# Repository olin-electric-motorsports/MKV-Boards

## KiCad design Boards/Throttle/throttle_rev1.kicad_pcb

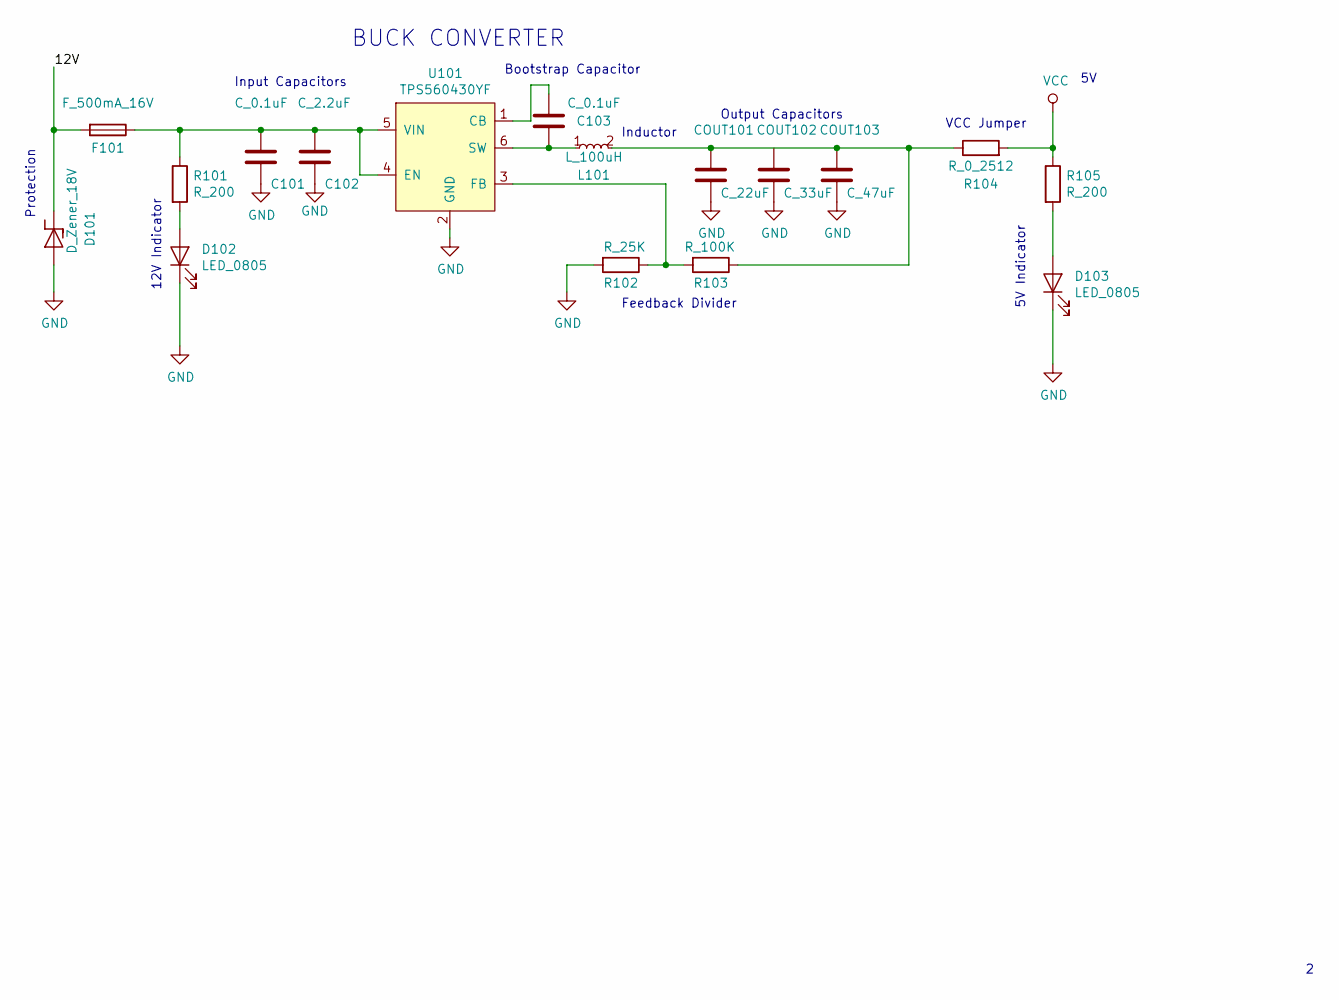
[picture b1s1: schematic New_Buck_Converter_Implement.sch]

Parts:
C101, C103: C_0.1uF; C_0805_OEM; MPN 478-3352-1-ND
C102: C_2.2uF; C_0603_1608Metric; MPN 311-1451-1-ND
COUT101: C_22uF; C_1206_OEM; MPN 445-11693-1-ND
COUT102: C_33uF; Fuse_1812; MPN 445-3924-1-ND
COUT103: C_47uF; C_0805_OEM; MPN 1276-6467-1-ND
D101: D_Zener_18V; DO-214AA; MPN SMBJ5355B-TPMSCT-ND
D102, D103: LED_0805; LED_0805_OEM; MPN 475-1410-1-ND
F101: F_500mA_16V; Fuse_1210; MPN 507-1786-1-ND
L101: L_100uH; MPN 445-15759-1-ND
R101, R105: R_200; R_0805_OEM; MPN RMCF0805JT200RCT-ND
R102: R_25K; R_0805_OEM; Digi-key Part Number CPF-A-0805B25KE
R103: R_100K; R_0805_OEM; MPN P100KCCT-ND
R104: R_0_2512; R_2512_OEM; MPN A121322CT-ND
U101: TPS560430YF; SOT-23-6_Handsoldering; MPN TPS560430YFDBVR

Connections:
+12V: D101.1 (K), F101.2; also elsewhere on the board
GND: C101.2, C102.2, COUT101.2, COUT102.2, COUT103.2, D101.2 (A), D102.1 (K), D103.1 (K), R102.2, U101.2 (GND); also elsewhere on the board
unnamed: C101.1, C102.1, F101.1, R101.1, U101.4 (EN), U101.5 (VIN)
unnamed: C103.1, L101.1, U101.6 (SW)
unnamed: C103.2, U101.1 (CB)
unnamed: D102.2 (A), R101.2
unnamed: D103.2 (A), R105.2
unnamed: R102.1, R103.2, U101.3 (FB)
VCC: R104.2, R105.1; also elsewhere on the board

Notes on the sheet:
Input Capacitors
12V Indicator
Protection
BUCK CONVERTER
Feedback Divider
Inductor
Bootstrap Capacitor
Output Capacitors
VCC Jumper
5V Indicator

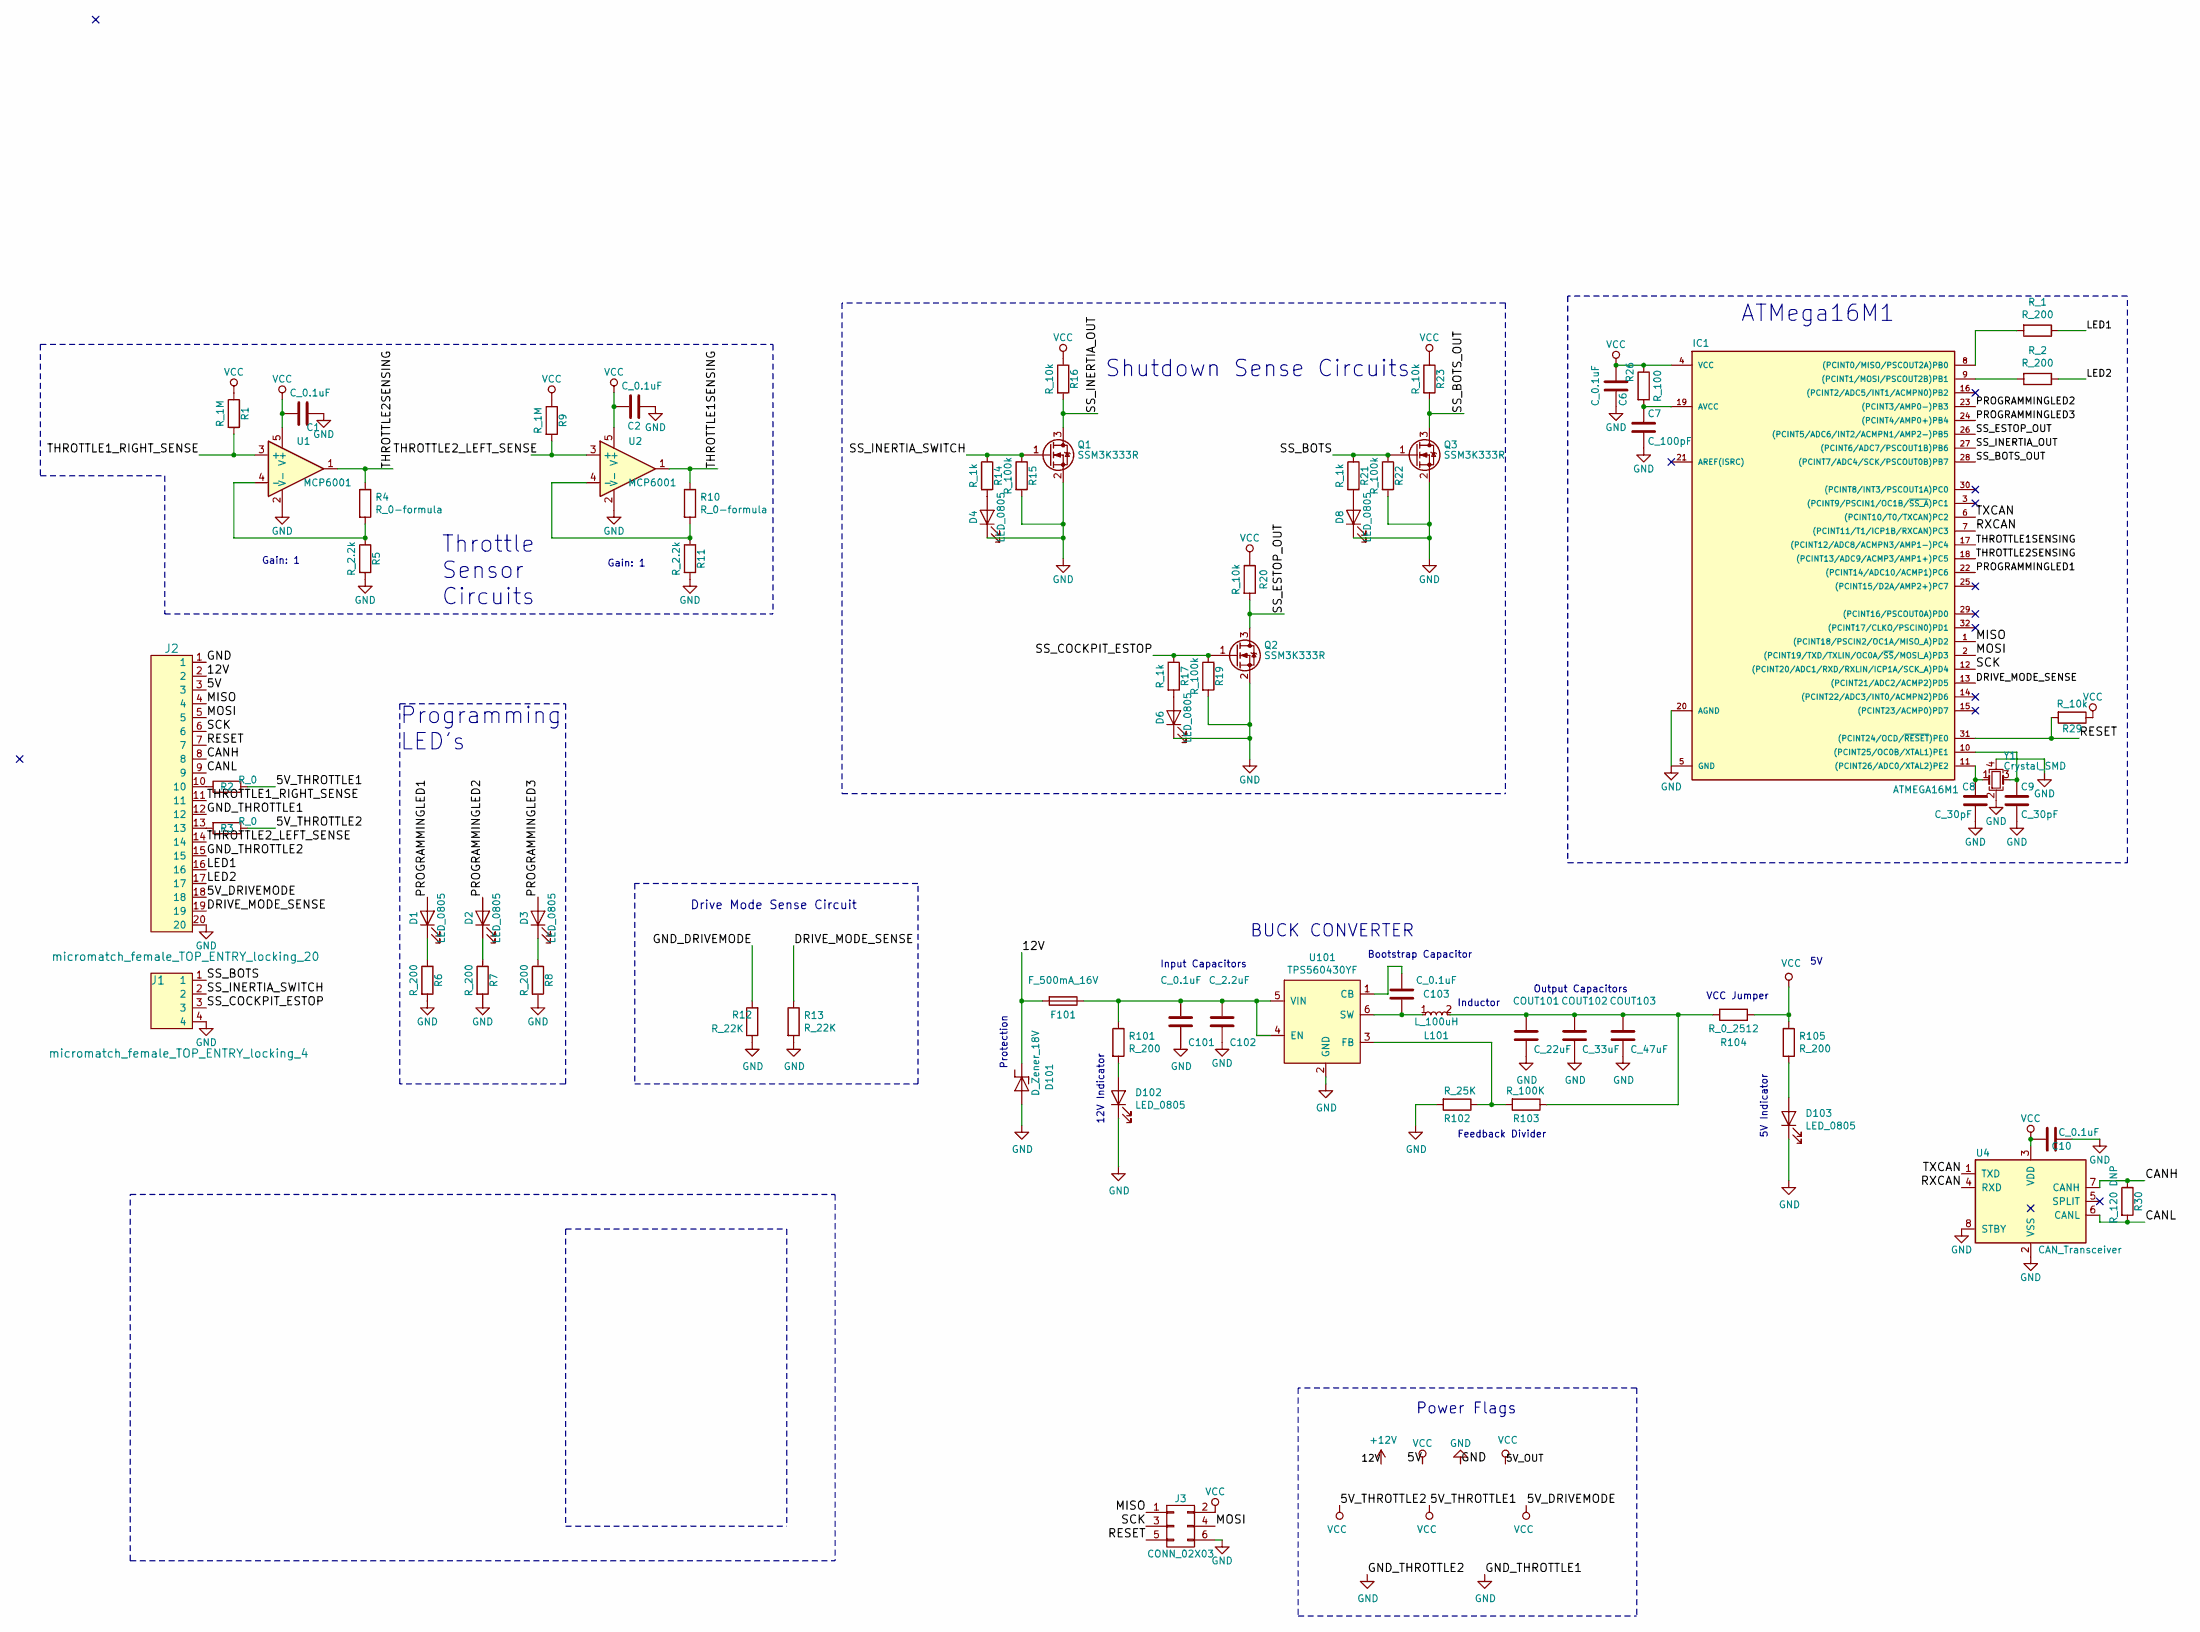
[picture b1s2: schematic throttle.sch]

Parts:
C1, C2, C6, C10, C101, C103: C_0.1uF; C_0805_OEM; MPN 478-3352-1-ND
C7: C_100pF; C_0805_OEM; MPN 732-7852-1-ND
C8, C9: C_30pF; C_0805_OEM; MPN 1276-1130-1-ND
C102: C_2.2uF; C_0603_1608Metric; MPN 311-1451-1-ND
COUT101: C_22uF; C_1206_OEM; MPN 445-11693-1-ND
COUT102: C_33uF; Fuse_1812; MPN 445-3924-1-ND
COUT103: C_47uF; C_0805_OEM; MPN 1276-6467-1-ND
D1, D2, D3, D4, D6, D8, D102, D103: LED_0805; LED_0805_OEM; MPN 475-1410-1-ND
D101: D_Zener_18V; DO-214AA; MPN SMBJ5355B-TPMSCT-ND
F101: F_500mA_16V; Fuse_1210; MPN 507-1786-1-ND
IC1: ATMEGA16M1; TQFP-32_7x7mm_Pitch0.8mm; MPN ATMEGA16M1-AU-ND
J1: micromatch_female_TOP_ENTRY_locking_4; micromatch_female_vert_4; MPN 338068-4
J2: micromatch_female_TOP_ENTRY_locking_20; micromatch_female_vert_20; MPN 2-338068-0
J3: CONN_02X03; Pin_Header_Straight_2x03; MPN 609-3234-ND
L101: L_100uH; MPN 445-15759-1-ND
Q1, Q2, Q3: SSM3K333R; SOT-23F; MPN SSM3K333RLFCT-ND
R1, R9: R_1M; R_0805_OEM; MPN RMCF0805JT1M00CT-ND
R2, R3: R_0; R_0603_1608Metric; MPN P0.0GCT-ND
R4, R10: R_0-formula; R_0603_1608Metric; MPN P0.0GCT-ND
R5, R11: R_2.2k; R_0805_OEM; MPN RMCF0805FT2K20CT-ND
R6, R7, R8, R101, R105: R_200; R_0805_OEM; MPN RMCF0805JT200RCT-ND
R12, R13: R_22K; R_0805_OEM; MPN RMCF0805JT22K0CT-ND
R14, R17, R21: R_1k; R_0805_OEM; MPN RNCP0805FTD1K00CT-ND
R15, R19, R22: R_100k; R_0805_OEM; MPN P100KCCT-ND
R16, R20, R23, R29: R_10k; R_0805_OEM; MPN CRS0805-FX-1002ELFCT-ND
R26: R_100; R_0805_OEM; MPN RNCP0805FTD100RCT-ND
R30: R_120 DNP; R_0805_OEM; MPN RMCF0805JT200RCT-ND
R102: R_25K; R_0805_OEM; Digi-key Part Number CPF-A-0805B25KE
R103: R_100K; R_0805_OEM; MPN P100KCCT-ND
R104: R_0_2512; R_2512_OEM; MPN A121322CT-ND
R_1, R_2: R_200; R_0805_OEM; MPN RMCF0805JT200RCT-ND
U1, U2: MCP6001; SOT-23-5_OEM; MPN MCP6001T-I/OTCT-ND
U4: CAN_Transceiver; SOIC-8_3.9x4.9mm_Pitch1.27mm_OEM; MPN MCP2561-E/SN-ND
U101: TPS560430YF; SOT-23-6_OEM; MPN TPS560430YFDBVR
Y1: Crystal_SMD; Crystal_SMD_FA238; MPN 887-1125-1-ND

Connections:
+12V: D101.1 (K), F101.2, J2.2
/CANH: J2.8, R30.1, U4.7 (CANH)
/CANL: J2.9, R30.2, U4.6 (CANL)
/DRIVE_MODE_SENSE: IC1.13 ((PCINT21/ADC2/ACMP2)PD5), J2.19, R13.1
/LED1: J2.16, R_1.1
/LED2: J2.17, R_2.1
/MISO: IC1.1 ((PCINT18/PSCIN2/OC1A/MISO_A)PD2), J2.4, J3.1
/MOSI: IC1.2 ((PCINT19/TXD/TXLIN/OC0A/~SS~/MOSI_A)PD3), J2.5, J3.4
/PROGRAMMINGLED1: D1.2 (A), IC1.22 ((PCINT14/ADC10/ACMP1)PC6)
/PROGRAMMINGLED2: D2.2 (A), IC1.23 ((PCINT3/AMP0-)PB3)
/PROGRAMMINGLED3: D3.2 (A), IC1.24 ((PCINT4/AMP0+)PB4)
/RESET: IC1.31 ((PCINT24/OCD/~RESET~)PE0), J2.7, J3.5, R29.2
/RXCAN: IC1.7 ((PCINT11/T1/ICP1B/RXCAN)PC3), U4.4 (RXD)
/SCK: IC1.12 ((PCINT20/ADC1/RXD/RXLIN/ICP1A/SCK_A)PD4), J2.6, J3.3
/SS_BOTS: J1.1, Q3.1 (G), R21.1, R22.1
/SS_BOTS_OUT: IC1.28 ((PCINT7/ADC4/SCK/PSCOUT0B)PB7), Q3.3 (D), R23.2
/SS_COCKPIT_ESTOP: J1.3, Q2.1 (G), R17.1, R19.1
/SS_ESTOP_OUT: IC1.26 ((PCINT5/ADC6/INT2/ACMPN1/AMP2-)PB5), Q2.3 (D), R20.2
/SS_INERTIA_OUT: IC1.27 ((PCINT6/ADC7/PSCOUT1B)PB6), Q1.3 (D), R16.2
/SS_INERTIA_SWITCH: J1.2, Q1.1 (G), R14.1, R15.1
/THROTTLE1SENSING: IC1.17 ((PCINT12/ADC8/ACMPN3/AMP1-)PC4), R10.1, U2.1
/THROTTLE1_RIGHT_SENSE: J2.11, R1.2, U1.3 (+)
/THROTTLE2SENSING: IC1.18 ((PCINT13/ADC9/ACMP3/AMP1+)PC5), R4.1, U1.1
/THROTTLE2_LEFT_SENSE: J2.14, R9.2, U2.3 (+)
/TXCAN: IC1.6 ((PCINT10/T0/TXCAN)PC2), U4.1 (TXD)
GND: C1.1, C2.1, C6.2, C7.2, C8.2, C9.2, C10.2, C101.2, C102.2, COUT101.2, COUT102.2, COUT103.2, D4.1 (K), D6.1 (K), D8.1 (K), D101.2 (A), D102.1 (K), D103.1 (K), IC1.5 (GND), IC1.20 (AGND), J1.4, J2.1, J2.12, J2.15, J2.20, J3.6, Q1.2 (S), Q2.2 (S), Q3.2 (S), R5.2, R6.2, R7.2, R8.2, R11.2, R12.1, R13.2, R15.2, R19.2, R22.2, R102.2, U1.2 (V-), U2.2 (V-), U4.2 (VSS), U4.8 (STBY), U101.2 (GND), Y1.2, Y1.4
unnamed: C7.1, IC1.19 (AVCC), R26.2
unnamed: C8.1, IC1.11 ((PCINT26/ADC0/XTAL2)PE2), Y1.1
unnamed: C9.1, IC1.10 ((PCINT25/OC0B/XTAL1)PE1), Y1.3
unnamed: C101.1, C102.1, F101.1, R101.1, U101.4 (EN), U101.5 (VIN)
unnamed: C103.1, L101.1, U101.6 (SW)
unnamed: C103.2, U101.1 (CB)
unnamed: D1.1 (K), R6.1
unnamed: D2.1 (K), R7.1
unnamed: D3.1 (K), R8.1
unnamed: D4.2 (A), R14.2
unnamed: D6.2 (A), R17.2
unnamed: D8.2 (A), R21.2
unnamed: D102.2 (A), R101.2
unnamed: D103.2 (A), R105.2
unnamed: IC1.8 ((PCINT0/MISO/PSCOUT2A)PB0), R_1.2
unnamed: IC1.9 ((PCINT1/MOSI/PSCOUT2B)PB1), R_2.2
unnamed: J2.10, R2.1
unnamed: J2.13, R3.2
unnamed: R4.2, R5.1, U1.4 (-)
unnamed: R10.2, R11.1, U2.4 (-)
unnamed: R102.1, R103.2, U101.3 (FB)
VCC: C1.2, C2.2, C6.1, C10.1, IC1.4 (VCC), J2.3, J2.18, J3.2, R1.1, R2.2, R3.1, R9.1, R16.1, R20.1, R23.1, R26.1, R29.1, R104.2, R105.1, U1.5 (V+), U2.5 (V+), U4.3 (VDD)

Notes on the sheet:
Shutdown Sense Circuits
Power Flags
ATMega16M1
Output Capacitors
VCC Jumper
5V Indicator
Programming LED's
Drive Mode Sense Circuit
Bootstrap Capacitor
Inductor
Feedback Divider
BUCK CONVERTER
Protection
12V Indicator
Input Capacitors
Gain: 1
Gain: 1
Throttle Sensor Circuits

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
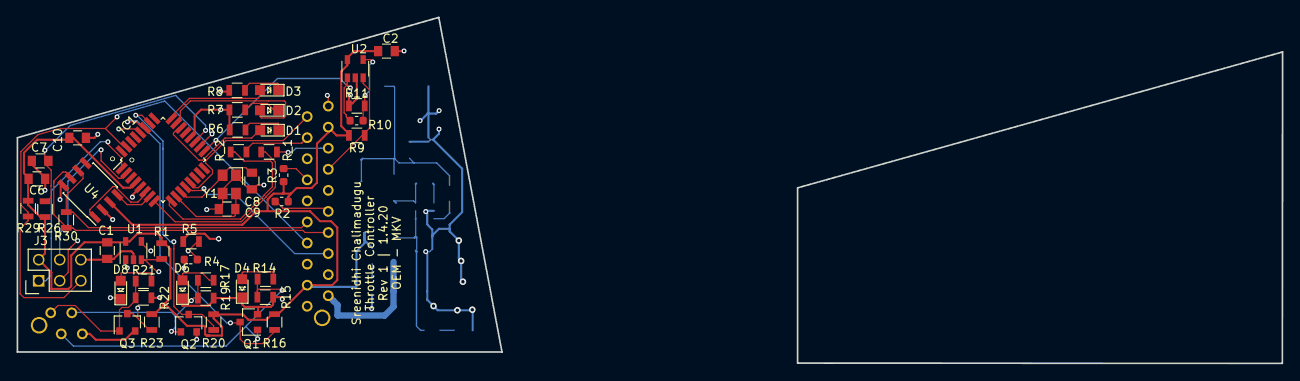
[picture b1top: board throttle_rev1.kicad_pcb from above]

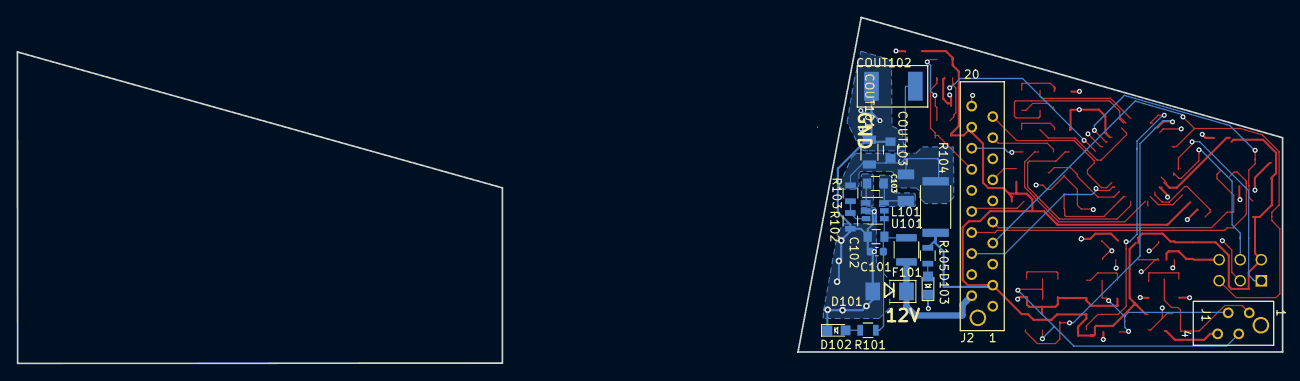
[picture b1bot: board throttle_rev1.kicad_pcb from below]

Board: 4 copper layers, 58.4 x 40.3 mm, 66 parts (19 on the bottom side), 49 nets.

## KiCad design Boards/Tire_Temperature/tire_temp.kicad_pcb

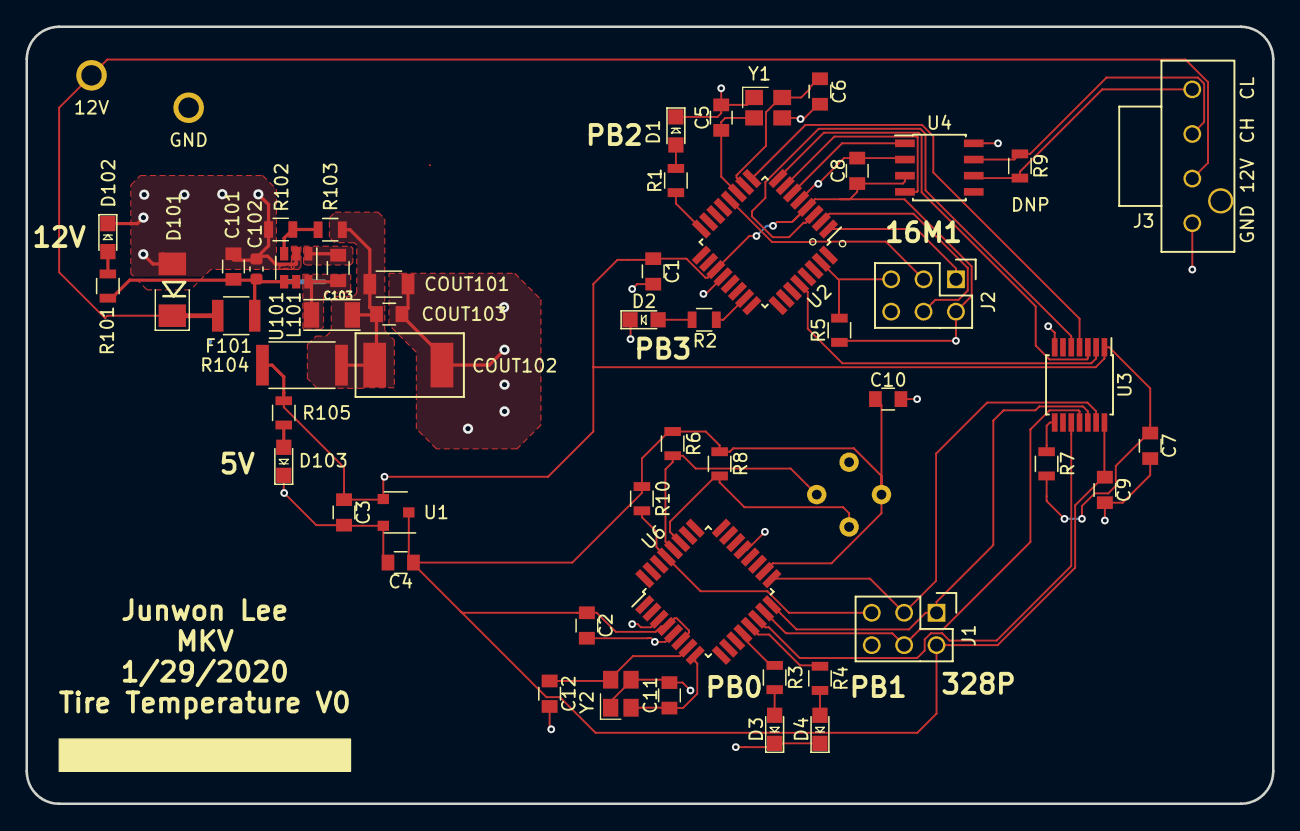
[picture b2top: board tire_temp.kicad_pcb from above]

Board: 2 copper layers, 97.8 x 61.0 mm, 56 parts (1 on the bottom side), 43 nets.

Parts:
12V: TP; tp_1.6mm
C1, C2, C3, C4, C7, C8, C9, C10, C101, C103: C_0.1uF; C_0805_OEM
C5, C6, C11, C12: C_30pF; C_0805_OEM
C102: C_2.2uF; C_0603_1608Metric
COUT101: C_22uF; C_1206_OEM
COUT102: C_33uF; Fuse_1812
COUT103: C_47uF; C_0805_OEM
D1, D2, D3, D4, D102, D103: LED_0805; LED_0805_OEM
D101: D_Zener_18V; DO-214AA
F101: F_500mA_16V; Fuse_1210
GND: TP; tp_1.6mm
J1, J2: CONN_02X03; Pin_Header_Straight_2x03
J3: UF_4_VT; Ultrafit_4
L101: L_100uH; L_100uH_OEM
R1, R2, R3, R4, R101, R105: R_200; R_0805_OEM
R5, R7, R10: R_10K; R_0805_OEM
R6, R8: R_4.7K; R_0805_OEM
R9: R_120_DNP; R_0805_OEM
R102: R_25K; R_0805_OEM
R103: R_100K; R_0805_OEM
R104: R_0_2512; R_2512_OEM
U1: LM3480; SOT-23-3_OEM
U2: ATMEGA16M1; TQFP-32_7x7mm_Pitch0.8mm
U3: TXB0104; TSSOP-14_4.4x5mm_P0.65mm
U4: MCP2561-E_SN; SOIC-8_3.9x4.9mm_Pitch1.27mm_OEM
U5: MLX90621ESF-BAB-000-TU
U6: ATmega328P-AU; TQFP-32_7x7mm_P0.8mm
U101: TPS560430YF; SOT-23-6_OEM
Y1, Y2: Crystal_SMD; Crystal_SMD_FA238

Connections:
/3.3V: C2.1, C4.1, C9.1, C10.1, J1.2, R6.1, R8.1, R10.1, U1.1, U3.14, U5.3, U6.4, U6.6, U6.18
/12V: 12V.1, D101.1, F101.2, J3.2
/CAN_H: J3.3, R9.1, U4.7
/CAN_L: J3.4, R9.2, U4.6
/CAN_RX: U2.7, U4.4
/CAN_TX: U2.6, U4.1
/CS3.3V: U3.10, U6.14
/CS5V: U2.3, U3.5
/MISO: J2.1, U2.1
/MISO3.3V: J1.1, U3.12, U6.16
/MISO5V: U2.8, U3.3
/MOSI: J2.4, U2.2
/MOSI3.3V: J1.4, U3.11, U6.15
/MOSI5V: U2.9, U3.4
/PROGRAMMINGLED1: R1.1, U2.16
/PROGRAMMINGLED2: R2.1, U2.23
/PROGRAMMINGLED3: R3.1, U6.12
/PROGRAMMINGLED4: R4.1, U6.13
/RESET: J2.5, R5.2, U2.31
/RESET3.3V: J1.5, R10.2, U6.29
/SCK: J2.3, U2.12
/SCK3.3V: J1.3, U3.13, U6.17
/SCK5V: U2.28, U3.2
/SCL: R6.2, U5.1, U6.28
/SDA: R8.2, U5.2, U6.27
GND: C1.2, C2.2, C3.2, C4.2, C5.2, C6.2, C7.2, C8.2, C9.2, C10.2, C11.2, C12.2, C101.2, C102.2, COUT101.2, COUT102.2, COUT103.2, D1.1, D2.1, D3.1, D4.1, D101.2, D102.1, D103.1, GND.1, J1.6, J2.6, J3.1, R102.2, U1.3, U2.5, U2.20, U3.7, U4.2, U4.8, U5.4, U6.3, U6.5, U6.21, U101.2, Y1.2, Y1.4, Y2.2, Y2.4
unnamed: C5.1, U2.11, Y1.1
unnamed: C6.1, U2.10, Y1.3
unnamed: C11.1, U6.8, Y2.1
unnamed: C12.1, U6.7, Y2.3
unnamed: C101.1, C102.1, F101.1, R101.1, U101.4, U101.5
unnamed: C103.1, U101.1
unnamed: C103.2, L101.1, U101.6
unnamed: COUT101.1, COUT102.1, COUT103.1, L101.2, R103.1, R104.1
unnamed: D1.2, R1.2
unnamed: D2.2, R2.2
unnamed: D3.2, R3.2
unnamed: D4.2, R4.2
unnamed: D102.2, R101.2
unnamed: D103.2, R105.2
unnamed: R7.1, U3.8
unnamed: R102.1, R103.2, U101.3
VCC: C1.1, C3.1, C7.1, C8.1, J2.2, R5.1, R7.2, R104.2, R105.1, U1.2, U2.4, U2.19, U3.1, U4.3

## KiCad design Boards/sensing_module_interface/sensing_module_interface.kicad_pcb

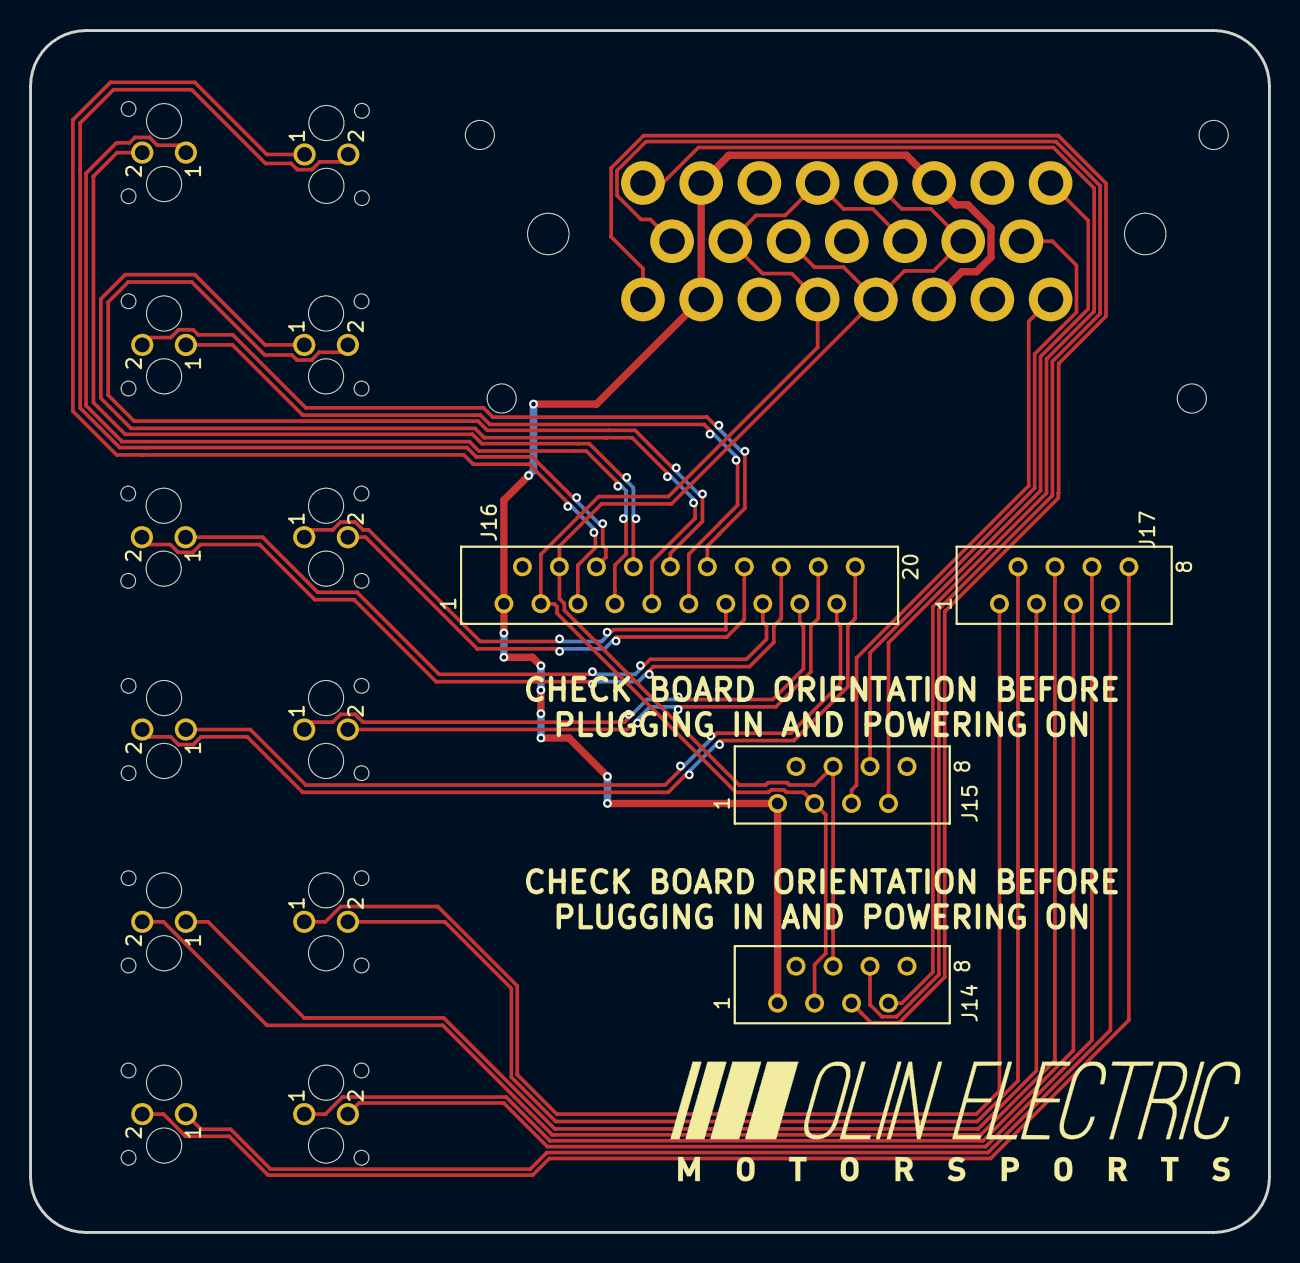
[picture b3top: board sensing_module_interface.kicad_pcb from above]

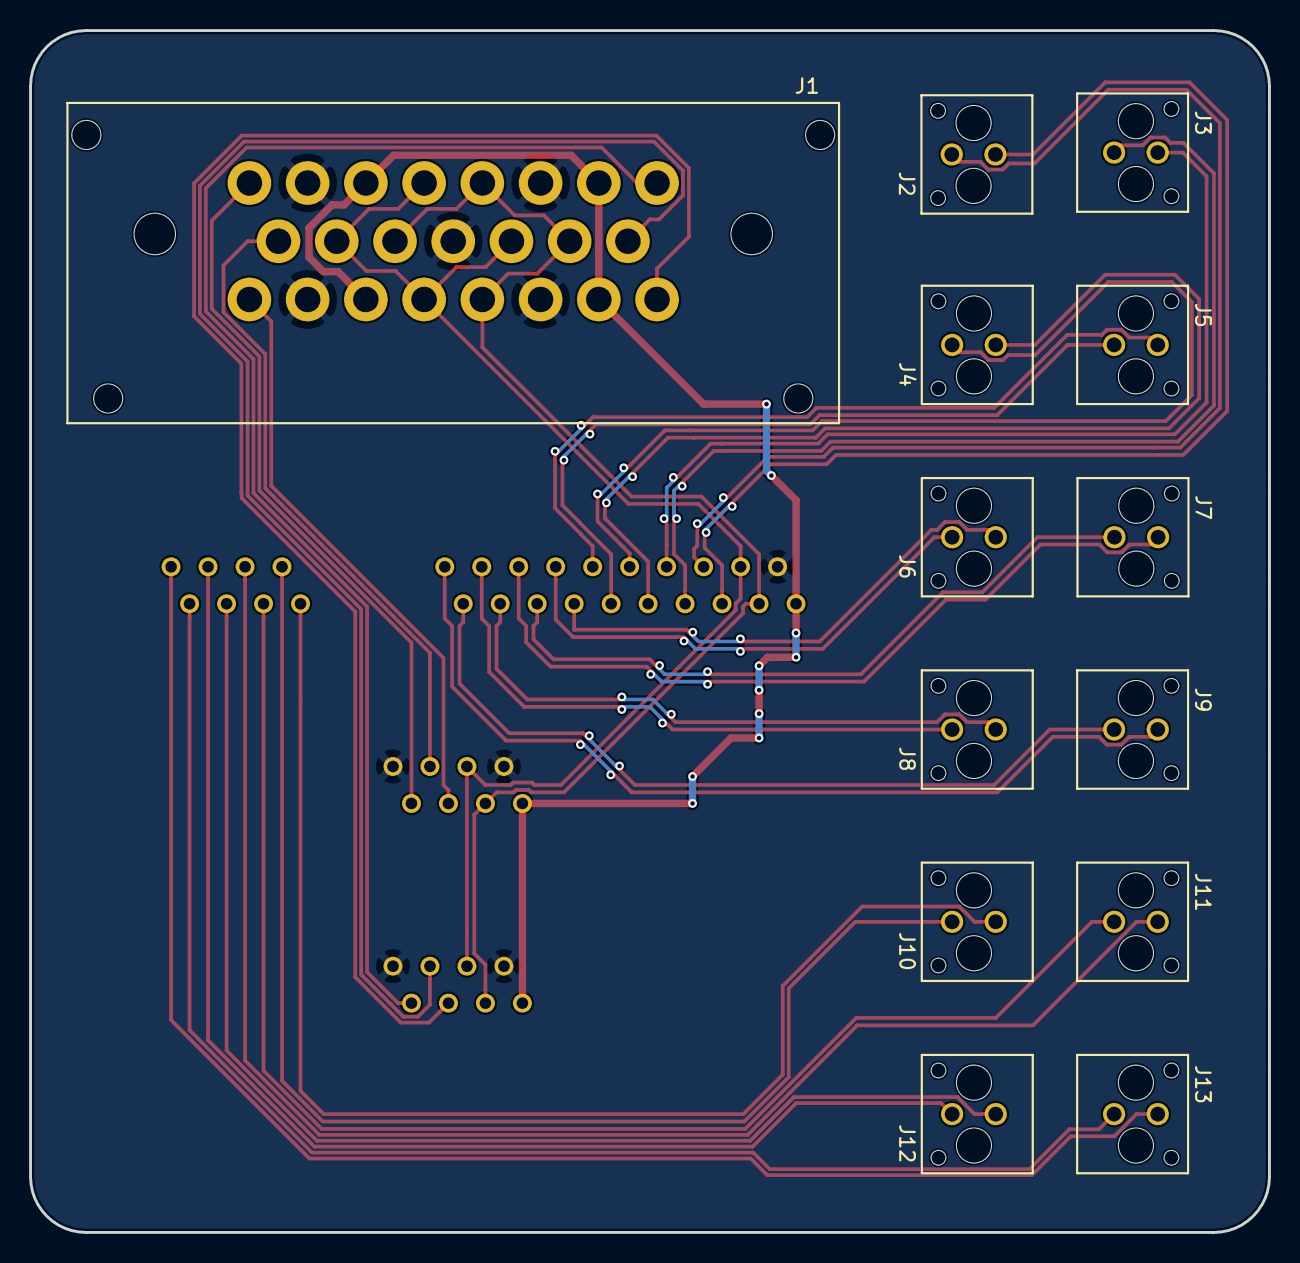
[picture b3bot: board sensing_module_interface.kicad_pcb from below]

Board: 2 copper layers, 85.1 x 82.6 mm, 17 parts (13 on the bottom side), 34 nets.

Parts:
J1: Ampseal_23_VT; Ampseal_23
J2, J3, J4, J5, J6, J7, J8, J9, J10, J11, J12, J13: MicroFit_V_2
J14, J15, J17: MM_M_VT_08; micromatch_female_ra_8
J16: MM_M_VT_20; micromatch_female_ra_20

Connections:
/12V: J1.2, J1.6, J1.17, J1.21, J14.1, J15.1, J16.1
/CAN_N: J1.5, J1.11, J1.14, J1.20, J14.4, J15.4, J16.4
/CAN_P: J1.4, J1.10, J1.13, J1.19, J14.3, J15.3, J16.3
/GND: J1.3, J1.7, J1.12, J1.18, J1.22, J14.2, J14.8, J15.2, J15.8, J16.2
/HALL_EFFECT_+: J1.1, J14.5
/HALL_EFFECT_-: J1.16, J14.7
/HALL_EFFECT_SENSE: J1.9, J14.6
/LINEAR_POT_+: J1.8, J15.5
/LINEAR_POT_-: J1.23, J15.7
/LINEAR_POT_SENSE: J1.15, J15.6
/STRAIN_GAUGE_1_+: J2.1, J16.5
/STRAIN_GAUGE_1_-: J2.2, J16.6
/STRAIN_GAUGE_2_+: J3.1, J16.7
/STRAIN_GAUGE_2_-: J3.2, J16.8
/STRAIN_GAUGE_3_+: J4.1, J16.9
/STRAIN_GAUGE_3_-: J4.2, J16.10
/STRAIN_GAUGE_4_+: J5.1, J16.11
/STRAIN_GAUGE_4_-: J5.2, J16.12
/STRAIN_GAUGE_5_+: J6.1, J16.13
/STRAIN_GAUGE_5_-: J6.2, J16.14
/STRAIN_GAUGE_6_+: J7.1, J16.15
/STRAIN_GAUGE_6_-: J7.2, J16.16
/STRAIN_GAUGE_7_+: J8.1, J16.17
/STRAIN_GAUGE_7_-: J8.2, J16.18
/STRAIN_GAUGE_8_+: J9.1, J16.19
/STRAIN_GAUGE_8_-: J9.2, J16.20
/STRAIN_GAUGE_9_+: J10.1, J17.1
/STRAIN_GAUGE_9_-: J10.2, J17.2
/STRAIN_GAUGE_10_+: J11.1, J17.3
/STRAIN_GAUGE_10_-: J11.2, J17.4
/STRAIN_GAUGE_11_+: J12.1, J17.5
/STRAIN_GAUGE_11_-: J12.2, J17.6
/STRAIN_GAUGE_12_+: J13.1, J17.7
/STRAIN_GAUGE_12_-: J13.2, J17.8

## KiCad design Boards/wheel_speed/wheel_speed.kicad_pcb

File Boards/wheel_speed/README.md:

# Wheel Speed Board

The purpose of these boards are to read the speeds coming from a hall effect sensor (which reads the hole pattern of the brake rotor) and report them over the CAN bus.

### Sensor

Multiple hall effect sensors were considered, but the sensor chosen was the [Littlefuse 55505](https://www.littelfuse.com/~/media/electronics/datasheets/hall_effect_sensors/littelfuse_hall_effect_sensors_55505_datasheet.pdf.pdf). This was chosen for simplicity, price, and because we already had one on hand to test with. It uses a simple 3 wire interface (power, ground, signal), which is fed to an interrupt pin for the MPU to read.

### Interface

This board interfaces to the main vehicle harness through an 8-pin Molex MicroFit connector. The pinout is:

1. +12V
2. GND
3. CAN_LOW
4. CAN_HIGH
5. SENSE_IN
6. GND
7. GND
8. +5V

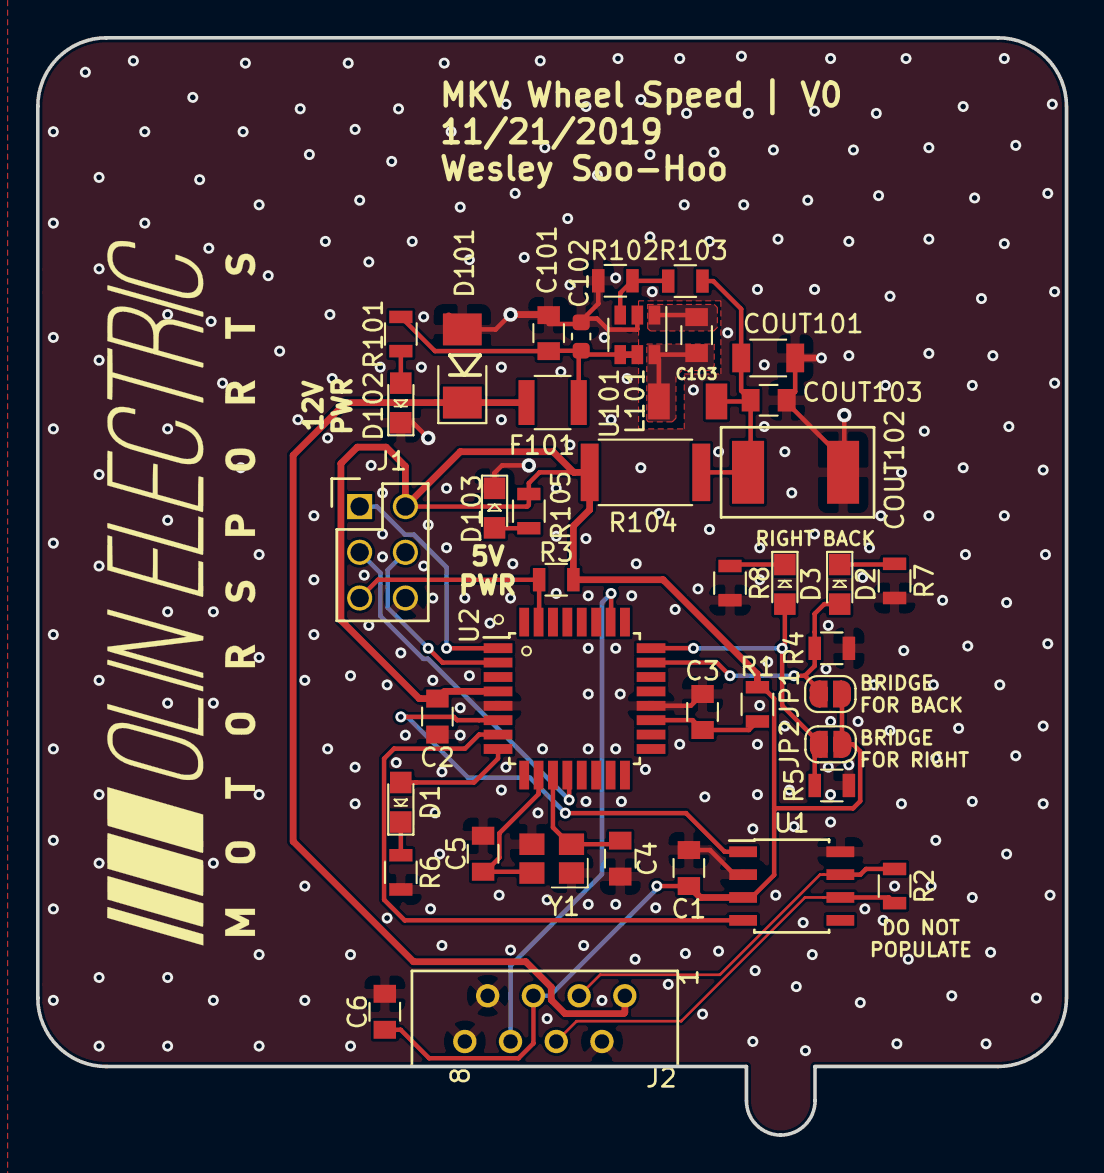
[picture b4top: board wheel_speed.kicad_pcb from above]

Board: 2 copper layers, 57.2 x 61.0 mm, 41 parts (0 on the bottom side), 28 nets.

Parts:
C1, C2, C6, C101, C103: C_0.1uF; C_0805_OEM
C3: C_100pF; C_0805_OEM
C4, C5: C_30pF; C_0805_OEM
C102: C_2.2uF; C_0603_1608Metric
COUT101: C_22uF; C_1206_OEM
COUT102: C_33uF; Fuse_1812
COUT103: C_47uF; C_0805_OEM
D1, D2, D3, D102, D103: LED_0805; LED_0805_OEM
D101: D_Zener_18V; DO-214AA
F101: F_500mA_16V; Fuse_1210
J1: CONN_02X03; Pin_Header_Straight_2x03
J2: MM_F_RA_08; micromatch_female_ra_8
JP1: FRONT_BACK; SolderJumper-2_P1.3mm_Open_RoundedPad1.0x1.5mm
JP2: LEFT_RIGHT; SolderJumper-2_P1.3mm_Open_RoundedPad1.0x1.5mm
L101: L_100uH
R1: R_100; R_0805_OEM
R2, R101, R105: R_200; R_0805_OEM
R3, R4, R5: R_10K; R_0805_OEM
R6, R7, R8: R_120; R_0805_OEM
R102: R_25K; R_0805_OEM
R103: R_100K; R_0805_OEM
R104: R_0_2512; R_2512_OEM
U1: MCP2561-E_SN; SOIC-8_3.9x4.9mm_Pitch1.27mm_OEM
U2: ATMEGA16M1; TQFP-32_7x7mm_Pitch0.8mm
U101: TPS560430YF; SOT-23-6_OEM
Y1: Crystal_SMD; Crystal_SMD_FA238

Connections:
/12V: D101.1, F101.2, J2.1
/CAN_HI: J2.3, R2.1, U1.7
/CAN_LO: J2.4, R2.2, U1.6
/CAN_RX: U1.4, U2.7
/CAN_TX: U1.1, U2.6
/DEBUG: D1.2, U2.8
/FRONT_SENSE: D2.2, JP1.1, R4.1, U2.23
/LEFT_SENSE: D3.2, JP2.1, R5.1, U2.24
/MISO: J1.1, U2.1
/MOSI: J1.4, U2.2
/RESET: J1.5, R3.2, U2.31
/SCK: J1.3, U2.12
/SENSE_IN: J2.6, U2.26
GND: C1.2, C2.2, C3.2, C4.2, C5.2, C6.1, C101.2, C102.2, COUT101.2, COUT102.2, COUT103.2, D101.2, D102.1, D103.1, J1.6, J2.2, J2.7, J2.8, R4.2, R5.2, R6.2, R7.2, R8.2, R102.2, U1.2, U1.8, U2.5, U2.20, U101.2, Y1.2, Y1.4
unnamed: C3.1, R1.2, U2.19
unnamed: C4.1, U2.11, Y1.1
unnamed: C5.1, U2.10, Y1.3
unnamed: C101.1, C102.1, F101.1, R101.1, U101.4, U101.5
unnamed: C103.1, U101.1
unnamed: C103.2, L101.1, U101.6
unnamed: COUT101.1, COUT102.1, COUT103.1, L101.2, R103.1, R104.1
unnamed: D1.1, R6.1
unnamed: D2.1, R7.1
unnamed: D3.1, R8.1
unnamed: D102.2, R101.2
unnamed: D103.2, R105.2
unnamed: R102.1, R103.2, U101.3
VCC: C1.1, C2.1, C6.2, J1.2, J2.5, JP1.2, JP2.2, R1.1, R3.1, R104.2, R105.1, U1.3, U2.4
